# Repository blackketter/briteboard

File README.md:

# briteboard

BriteBoard is a Teensy 3.6-based keyboard with:

- 5x14 key matrix
- LCD display with capacitive touchscreen
- Audio amplifier and speaker
- USB host port for external mouse or keyboard
- Ambient light sensor

Runs the [britepad](https://github.com/blackketter/britepad) software.

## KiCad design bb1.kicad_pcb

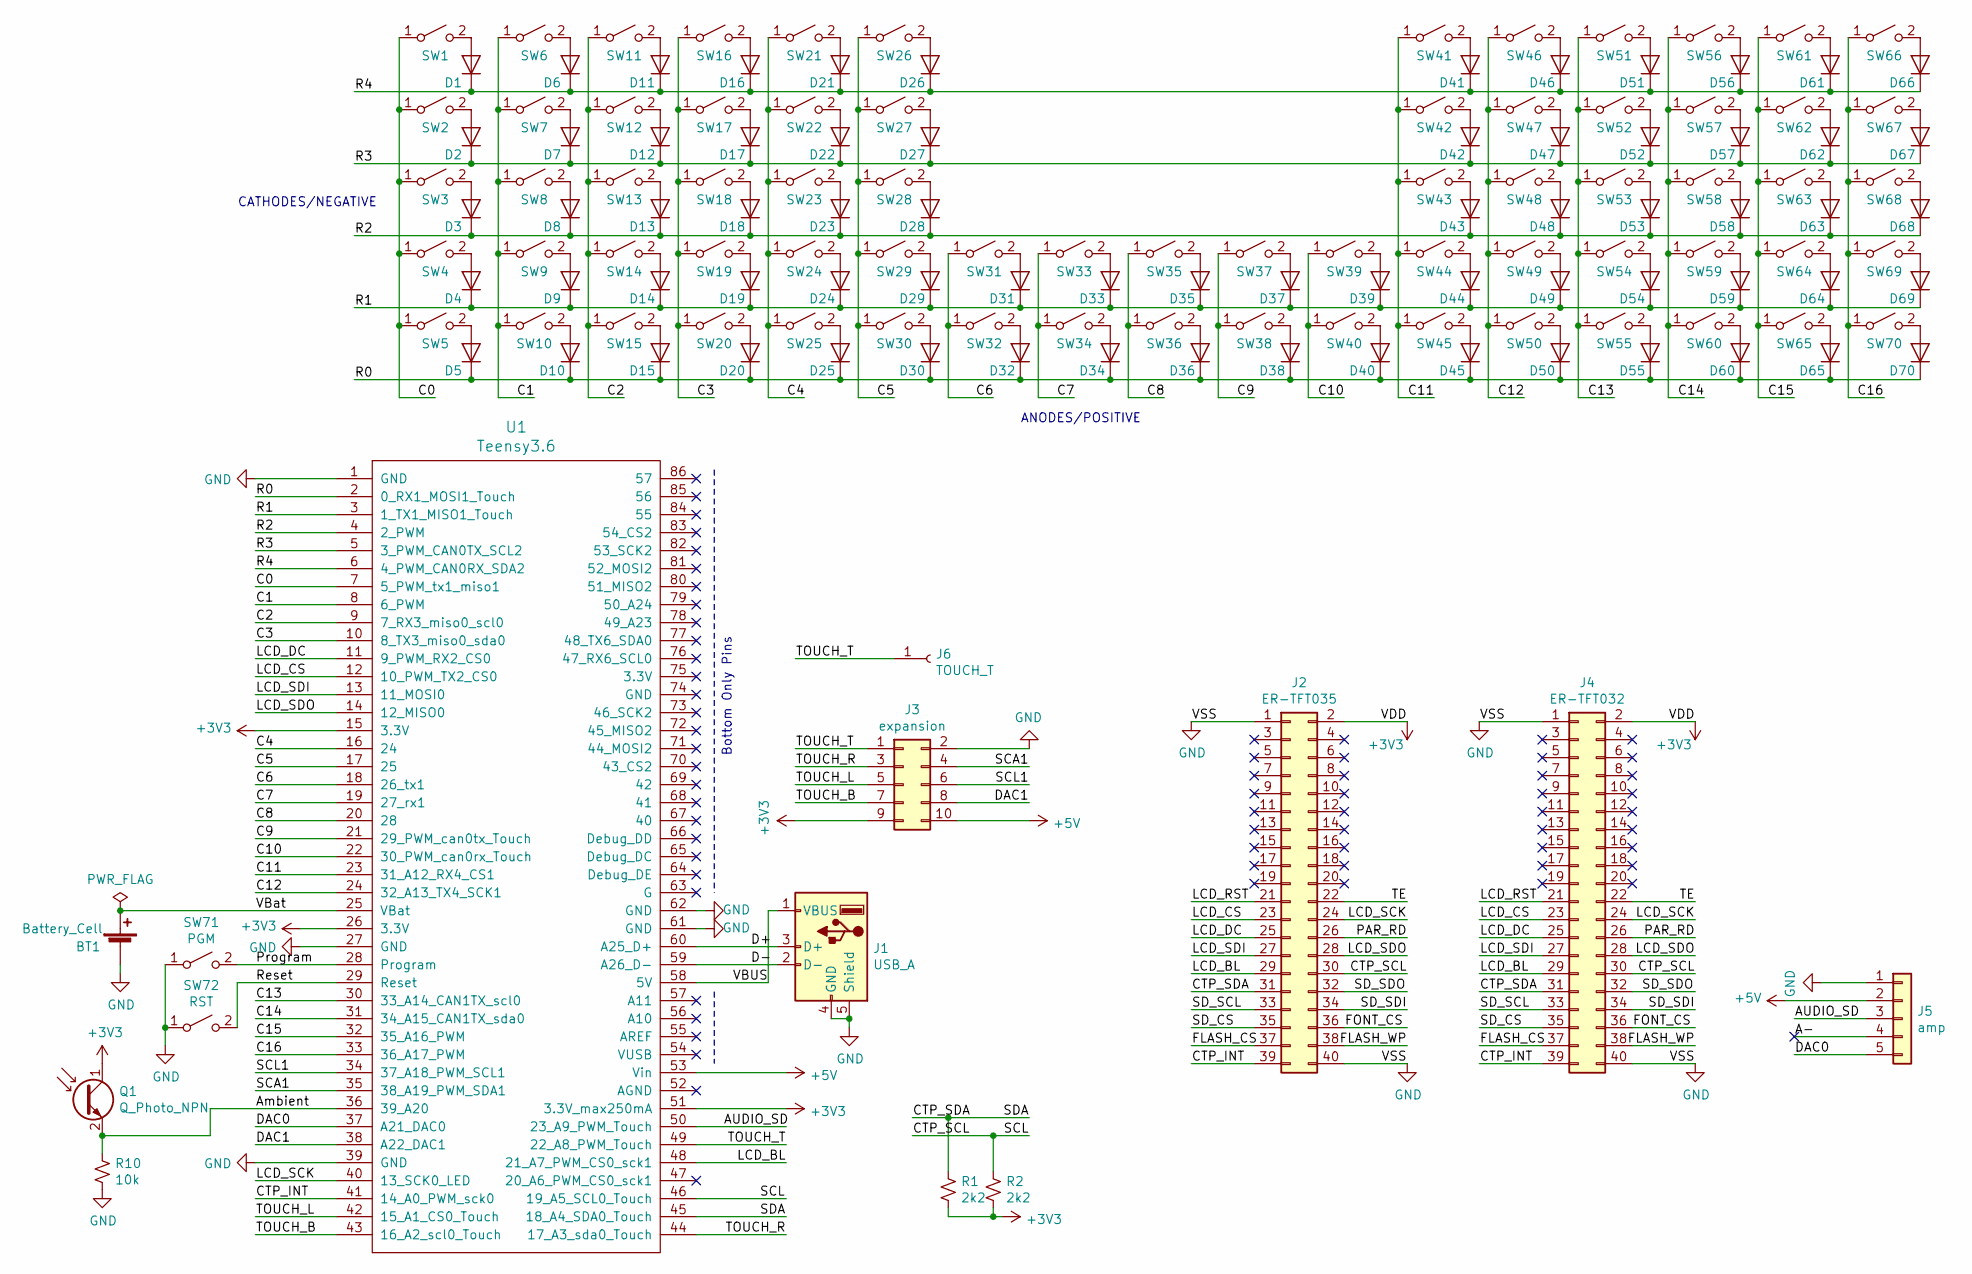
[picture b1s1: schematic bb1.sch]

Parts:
BT1: Battery_Cell; BC-2003
D1, D2, D3, D4, D5, D6, D7, D8, D9, D10, D11, D12, D13, D14, D15, D16, D17, D18, D19, D20, D21, D22, D23, D24, D25, D26, D27, D28, D29, D30, D31, D32, D33, D34, D35, D36, D37, D38, D39, D40, D41, D42, D43, D44, D45, D46, D47, D48, D49, D50, D51, D52, D53, D54, D55, D56, D57, D58, D59, D60, D61, D62, D63, D64, D65, D66, D67, D68, D69, D70: 1N914; D_DO-35_SOD27_P7.62mm_Horizontal
J1: USB_A; USB_A_Female_UE27AC54100
J2: ER-TFT035; PinSocket_2x20_P2.54mm_Vertical
J3: expansion; PinSocket_2x05_P2.54mm_Vertical
J4: ER-TFT032; PinSocket_2x20_P2.54mm_Vertical
J5: amp; PinSocket_1x05_P2.54mm_Vertical
J6: TOUCH_T; PinSocket_1x01_P2.54mm_Vertical
Q1: Q_Photo_NPN; LED_D5.0mm_FlatTop
R1, R2: 2k2; 0603
R10: 10k; 0603
SW1, SW2, SW3, SW4, SW5, SW6, SW7, SW8, SW9, SW10, SW11, SW12, SW13, SW14, SW15, SW16, SW17, SW18, SW19, SW20, SW21, SW22, SW23, SW24, SW25, SW26, SW27, SW28, SW29, SW30, SW31, SW32, SW33, SW34, SW35, SW36, SW37, SW38, SW39, SW40, SW41, SW42, SW43, SW44, SW45, SW46, SW47, SW48, SW49, SW50, SW51, SW52, SW53, SW54, SW55, SW56, SW57, SW58, SW59, SW60, SW61, SW62, SW63, SW64, SW65, SW66, SW67, SW68, SW69, SW70: SW_SPST; PG1350_rotatable
SW71: PGM; EVQPSL
SW72: RST; EVQPSL
U1: Teensy3.6; Teensy35_36

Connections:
+3V3: J2.2, J3.9, J4.2, Q1.1 (C), R1.2, R2.2, U1.15 (3.3V), U1.26 (3.3V), U1.51 (3.3V_max250mA)
+5V: J3.10, J5.2, U1.53 (Vin)
/AUDIO_SD: J5.3, U1.50 (23_A9_PWM_Touch)
/Ambient: Q1.2 (E), R10.1, U1.36 (39_A20)
/C0: SW1.1 (A), SW2.1 (A), SW3.1 (A), SW4.1 (A), SW5.1 (A), U1.7 (5_PWM_tx1_miso1)
/C1: SW6.1 (A), SW7.1 (A), SW8.1 (A), SW9.1 (A), SW10.1 (A), U1.8 (6_PWM)
/C2: SW11.1 (A), SW12.1 (A), SW13.1 (A), SW14.1 (A), SW15.1 (A), U1.9 (7_RX3_miso0_scl0)
/C3: SW16.1 (A), SW17.1 (A), SW18.1 (A), SW19.1 (A), SW20.1 (A), U1.10 (8_TX3_miso0_sda0)
/C4: SW21.1 (A), SW22.1 (A), SW23.1 (A), SW24.1 (A), SW25.1 (A), U1.16 (24)
/C5: SW26.1 (A), SW27.1 (A), SW28.1 (A), SW29.1 (A), SW30.1 (A), U1.17 (25)
/C6: SW31.1 (A), SW32.1 (A), U1.18 (26_tx1)
/C7: SW33.1 (A), SW34.1 (A), U1.19 (27_rx1)
/C8: SW35.1 (A), SW36.1 (A), U1.20 (28)
/C9: SW37.1 (A), SW38.1 (A), U1.21 (29_PWM_can0tx_Touch)
/C10: SW39.1 (A), SW40.1 (A), U1.22 (30_PWM_can0rx_Touch)
/C11: SW41.1 (A), SW42.1 (A), SW43.1 (A), SW44.1 (A), SW45.1 (A), U1.23 (31_A12_RX4_CS1)
/C12: SW46.1 (A), SW47.1 (A), SW48.1 (A), SW49.1 (A), SW50.1 (A), U1.24 (32_A13_TX4_SCK1)
/C13: SW51.1 (A), SW52.1 (A), SW53.1 (A), SW54.1 (A), SW55.1 (A), U1.30 (33_A14_CAN1TX_scl0)
/C14: SW56.1 (A), SW57.1 (A), SW58.1 (A), SW59.1 (A), SW60.1 (A), U1.31 (34_A15_CAN1TX_sda0)
/C15: SW61.1 (A), SW62.1 (A), SW63.1 (A), SW64.1 (A), SW65.1 (A), U1.32 (35_A16_PWM)
/C16: SW66.1 (A), SW67.1 (A), SW68.1 (A), SW69.1 (A), SW70.1 (A), U1.33 (36_A17_PWM)
/CTP_INT: J2.39, J4.39, U1.41 (14_A0_PWM_sck0)
/CTP_SCL: J2.30, J4.30, R2.1, U1.46 (19_A5_SCL0_Touch)
/CTP_SDA: J2.31, J4.31, R1.1, U1.45 (18_A4_SDA0_Touch)
/D+: J1.3 (D+), U1.60 (A25_D+)
/D-: J1.2 (D-), U1.59 (A26_D-)
/DAC0: J5.5, U1.37 (A21_DAC0)
/DAC1: J3.8, U1.38 (A22_DAC1)
/FLASH_CS: J2.37, J4.37
/FLASH_WP: J2.38, J4.38
/FONT_CS: J2.36, J4.36
/LCD_BL: J2.29, J4.29, U1.48 (21_A7_PWM_CS0_sck1)
/LCD_CS: J2.23, J4.23, U1.12 (10_PWM_TX2_CS0)
/LCD_DC: J2.25, J4.25, U1.11 (9_PWM_RX2_CS0)
/LCD_RST: J2.21, J4.21
/LCD_SCK: J2.24, J4.24, U1.40 (13_SCK0_LED)
/LCD_SDI: J2.27, J4.27, U1.13 (11_MOSI0)
/LCD_SDO: J2.28, J4.28, U1.14 (12_MISO0)
/PAR_RD: J2.26, J4.26
/Program: SW71.2 (B), U1.28 (Program)
/R0: D5.1 (K), D10.1 (K), D15.1 (K), D20.1 (K), D25.1 (K), D30.1 (K), D32.1 (K), D34.1 (K), D36.1 (K), D38.1 (K), D40.1 (K), D45.1 (K), D50.1 (K), D55.1 (K), D60.1 (K), D65.1 (K), D70.1 (K), U1.2 (0_RX1_MOSI1_Touch)
/R1: D4.1 (K), D9.1 (K), D14.1 (K), D19.1 (K), D24.1 (K), D29.1 (K), D31.1 (K), D33.1 (K), D35.1 (K), D37.1 (K), D39.1 (K), D44.1 (K), D49.1 (K), D54.1 (K), D59.1 (K), D64.1 (K), D69.1 (K), U1.3 (1_TX1_MISO1_Touch)
/R2: D3.1 (K), D8.1 (K), D13.1 (K), D18.1 (K), D23.1 (K), D28.1 (K), D43.1 (K), D48.1 (K), D53.1 (K), D58.1 (K), D63.1 (K), D68.1 (K), U1.4 (2_PWM)
/R3: D2.1 (K), D7.1 (K), D12.1 (K), D17.1 (K), D22.1 (K), D27.1 (K), D42.1 (K), D47.1 (K), D52.1 (K), D57.1 (K), D62.1 (K), D67.1 (K), U1.5 (3_PWM_CAN0TX_SCL2)
/R4: D1.1 (K), D6.1 (K), D11.1 (K), D16.1 (K), D21.1 (K), D26.1 (K), D41.1 (K), D46.1 (K), D51.1 (K), D56.1 (K), D61.1 (K), D66.1 (K), U1.6 (4_PWM_CAN0RX_SDA2)
/Reset: SW72.2 (B), U1.29 (Reset)
/SCA1: J3.4, U1.35 (38_A19_PWM_SDA1)
/SCL1: J3.6, U1.34 (37_A18_PWM_SCL1)
/SD_CS: J2.35, J4.35
/SD_SCL: J2.33, J4.33
/SD_SDI: J2.34, J4.34
/SD_SDO: J2.32, J4.32
/TE: J2.22, J4.22
/TOUCH_B: J3.7, U1.43 (16_A2_scl0_Touch)
/TOUCH_L: J3.5, U1.42 (15_A1_CS0_Touch)
/TOUCH_R: J3.3, U1.44 (17_A3_sda0_Touch)
/TOUCH_T: J3.1, J6.1, U1.49 (22_A8_PWM_Touch)
/VBUS: J1.1 (VBUS), U1.58 (5V)
/VBat: BT1.1 (+), U1.25 (VBat)
GND: BT1.2 (-), J1.4 (GND), J1.5 (Shield), J2.1, J2.40, J3.2, J4.1, J4.40, J5.1, R10.2, SW71.1 (A), SW72.1 (A), U1.1 (GND), U1.27 (GND), U1.39 (GND), U1.61 (GND), U1.62 (GND)
unnamed: D1.2 (A), SW1.2 (B)
unnamed: D2.2 (A), SW2.2 (B)
unnamed: D3.2 (A), SW3.2 (B)
unnamed: D4.2 (A), SW4.2 (B)
unnamed: D5.2 (A), SW5.2 (B)
unnamed: D6.2 (A), SW6.2 (B)
unnamed: D7.2 (A), SW7.2 (B)
unnamed: D8.2 (A), SW8.2 (B)
unnamed: D9.2 (A), SW9.2 (B)
unnamed: D10.2 (A), SW10.2 (B)
unnamed: D11.2 (A), SW11.2 (B)
unnamed: D12.2 (A), SW12.2 (B)
unnamed: D13.2 (A), SW13.2 (B)
unnamed: D14.2 (A), SW14.2 (B)
unnamed: D15.2 (A), SW15.2 (B)
unnamed: D16.2 (A), SW16.2 (B)
unnamed: D17.2 (A), SW17.2 (B)
unnamed: D18.2 (A), SW18.2 (B)
unnamed: D19.2 (A), SW19.2 (B)
unnamed: D20.2 (A), SW20.2 (B)
unnamed: D21.2 (A), SW21.2 (B)
unnamed: D22.2 (A), SW22.2 (B)
unnamed: D23.2 (A), SW23.2 (B)
unnamed: D24.2 (A), SW24.2 (B)
unnamed: D25.2 (A), SW25.2 (B)
unnamed: D26.2 (A), SW26.2 (B)
unnamed: D27.2 (A), SW27.2 (B)
unnamed: D28.2 (A), SW28.2 (B)
unnamed: D29.2 (A), SW29.2 (B)
unnamed: D30.2 (A), SW30.2 (B)
unnamed: D31.2 (A), SW31.2 (B)
unnamed: D32.2 (A), SW32.2 (B)
unnamed: D33.2 (A), SW33.2 (B)
unnamed: D34.2 (A), SW34.2 (B)
unnamed: D35.2 (A), SW35.2 (B)
unnamed: D36.2 (A), SW36.2 (B)
unnamed: D37.2 (A), SW37.2 (B)
unnamed: D38.2 (A), SW38.2 (B)
unnamed: D39.2 (A), SW39.2 (B)
unnamed: D40.2 (A), SW40.2 (B)
unnamed: D41.2 (A), SW41.2 (B)
unnamed: D42.2 (A), SW42.2 (B)
unnamed: D43.2 (A), SW43.2 (B)
unnamed: D44.2 (A), SW44.2 (B)
unnamed: D45.2 (A), SW45.2 (B)
unnamed: D46.2 (A), SW46.2 (B)
unnamed: D47.2 (A), SW47.2 (B)
unnamed: D48.2 (A), SW48.2 (B)
unnamed: D49.2 (A), SW49.2 (B)
unnamed: D50.2 (A), SW50.2 (B)
unnamed: D51.2 (A), SW51.2 (B)
unnamed: D52.2 (A), SW52.2 (B)
unnamed: D53.2 (A), SW53.2 (B)
unnamed: D54.2 (A), SW54.2 (B)
unnamed: D55.2 (A), SW55.2 (B)
unnamed: D56.2 (A), SW56.2 (B)
unnamed: D57.2 (A), SW57.2 (B)
unnamed: D58.2 (A), SW58.2 (B)
unnamed: D59.2 (A), SW59.2 (B)
unnamed: D60.2 (A), SW60.2 (B)
unnamed: D61.2 (A), SW61.2 (B)
unnamed: D62.2 (A), SW62.2 (B)
unnamed: D63.2 (A), SW63.2 (B)
unnamed: D64.2 (A), SW64.2 (B)
unnamed: D65.2 (A), SW65.2 (B)
unnamed: D66.2 (A), SW66.2 (B)
unnamed: D67.2 (A), SW67.2 (B)
unnamed: D68.2 (A), SW68.2 (B)
unnamed: D69.2 (A), SW69.2 (B)
unnamed: D70.2 (A), SW70.2 (B)

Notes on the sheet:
Bottom Only Pins
ANODES/POSITIVE
CATHODES/NEGATIVE

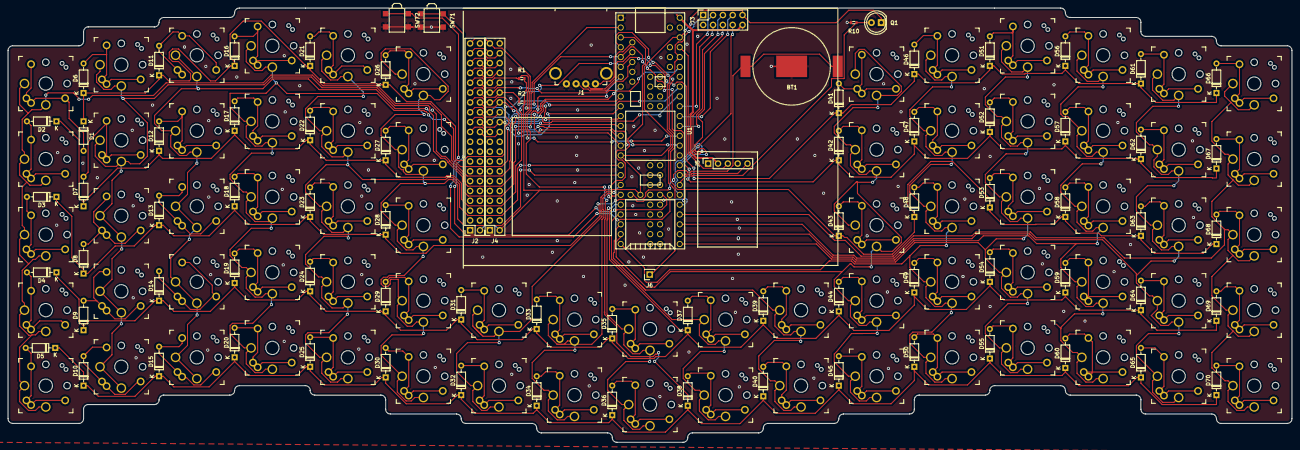
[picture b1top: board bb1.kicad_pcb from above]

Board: 2 copper layers, 331.5 x 112.1 mm, 154 parts (0 on the bottom side), 130 nets.

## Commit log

2018-12-14 First pass on bb1 pcb. Ordered via elecrow
2018-12-14 Final save after order
2019-01-08 Added schematics and datasheets
2020-01-25 Last changes, finally committed.
2020-01-25 Added README and BOM
2020-01-25 Not used
2020-01-25 Add pics.
2020-01-25 More pics
